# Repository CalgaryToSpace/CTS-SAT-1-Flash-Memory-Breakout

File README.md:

# CTS-SAT-1-Flash-Memory-Breakout

A breakout board for the CTS-SAT-1 flash memory module, used on the Onboard Computer (OBC) of the CTS-SAT-1 satellite.

The target memory modules is the `S70FL01GSAGMFI011` (`S70FL01`). This PCB is compatible with many similar memory modules in the same family.

This PCB is pin-compatible with the following memory modules:
* Infineon `S70FL01GSAGMFI011` (`S70FL01`)
* Infineon `S25FL512SDVFG1` (`S25FL512`)
* Cypress `25HL01GTFI01` (`25HL01`)

## PCB Renderings

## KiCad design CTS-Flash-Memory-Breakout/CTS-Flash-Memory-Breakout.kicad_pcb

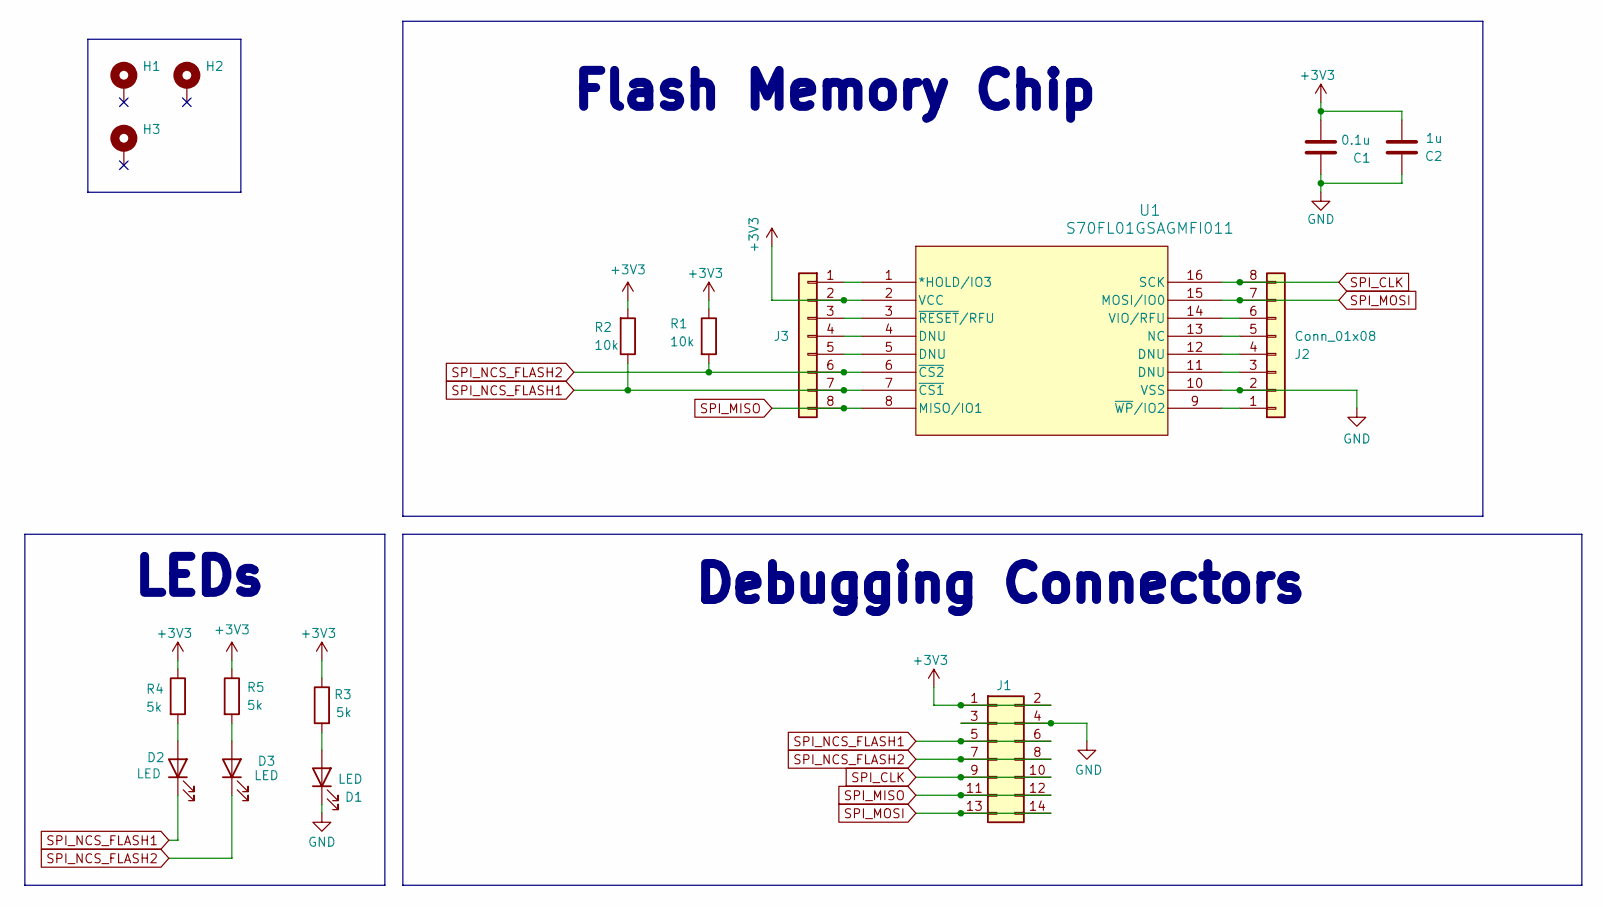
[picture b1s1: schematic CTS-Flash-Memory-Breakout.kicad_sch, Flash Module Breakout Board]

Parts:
C1: 0.1u; C_1206_3216Metric_Pad1.33x1.80mm_HandSolder
C2: 1u; C_1206_3216Metric_Pad1.33x1.80mm_HandSolder
D1, D2, D3: LED; LED_1206_3216Metric_Pad1.42x1.75mm_HandSolder
H1, H2, H3: MountingHole_Pad; MountingHole_2.2mm_M2_DIN965_Pad
J1: Conn_02x07_Counter_Clockwise; PinHeader_2x07_P2.54mm_Vertical
J2, J3: Conn_01x08; PinHeader_1x08_P2.54mm_Vertical
R1, R2: 10k; R_1206_3216Metric_Pad1.30x1.75mm_HandSolder
R3, R4, R5: 5k; R_1206_3216Metric_Pad1.30x1.75mm_HandSolder
U1: S70FL01GSAGMFI011; SOIC-16W_7.5x10.3mm_P1.27mm

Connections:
+3V3: C1.2, C2.2, J1.1, J1.2, J3.2, R1.1, R2.2, R3.1, R4.1, R5.1, U1.2 (VCC)
GND: C1.1, C2.1, D1.1 (K), J1.3, J1.4, J2.2, U1.10 (VSS)
unnamed: D1.2 (A), R3.2
unnamed: D2.2 (A), R4.2
unnamed: D3.2 (A), R5.2
unnamed: J2.1, U1.9 (~WP/IO2)
unnamed: J2.3, U1.11 (DNU)
unnamed: J2.4, U1.12 (DNU)
unnamed: J2.5, U1.13 (NC)
unnamed: J2.6, U1.14 (VIO/RFU)
unnamed: J3.1, U1.1 (*HOLD/IO3)
unnamed: J3.3, U1.3 (~RESET/RFU)
unnamed: J3.4, U1.4 (DNU)
unnamed: J3.5, U1.5 (DNU)
SPI_CLK: J1.9, J1.10, J2.8, U1.16 (SCK)
SPI_MISO: J1.11, J1.12, J3.8, U1.8 (MISO/IO1)
SPI_MOSI: J1.13, J1.14, J2.7, U1.15 (MOSI/IO0)
SPI_NCS_FLASH1: D2.1 (K), J1.5, J1.6, J3.7, R2.1, U1.7 (~CS1)
SPI_NCS_FLASH2: D3.1 (K), J1.7, J1.8, J3.6, R1.2, U1.6 (~CS2)

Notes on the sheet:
LEDs
Debugging Connectors
Flash Memory Chip

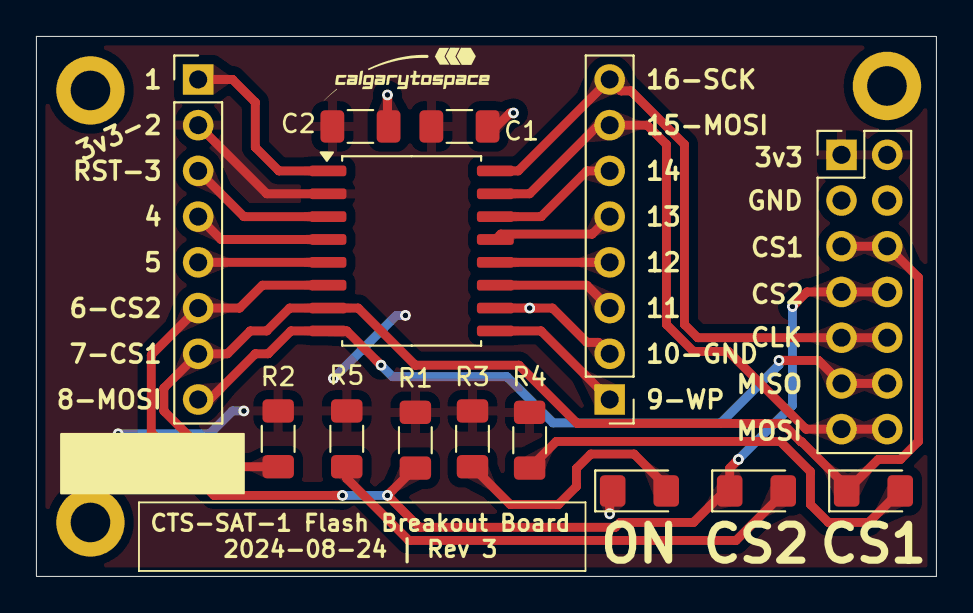
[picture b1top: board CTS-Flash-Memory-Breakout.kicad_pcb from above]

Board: 2 copper layers, 50.0 x 30.0 mm, 17 parts (0 on the bottom side), 19 nets.

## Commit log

2024-05-08 Created project
    Created project and added CAD files to repository
2024-05-08 Silkscreen modifications
    Added CTS logo to board alongside date and revision #
2024-05-08 Created production files
    Created production files
2024-06-07 Update errata on schematic, add rendering and part number to README
2024-06-08 Create Rev 2 board
    - Breakout every pin on the chip to new headers
    - Fix missing inline resistors for LEDs
    - Add extra bulk capacitance
    - Reroute with wide traces
    - More silkscreens
    - Silkscreens for writing notes/labels in Sharpie
2024-06-08 Update render images
2024-06-21 Create Rev 2
    - Add mounting holes
    - Improve routing
2024-08-24 Create Rev 3 with CS label fix, teardrops
    Changes from Rev 2:
    * Fixed bad CS0/CS1 label to CS1/CS2.
    * Added teardrops
    * Fixed some routing to move traces farther from pads
2024-08-24 Re-plot Rev 3 schematic
